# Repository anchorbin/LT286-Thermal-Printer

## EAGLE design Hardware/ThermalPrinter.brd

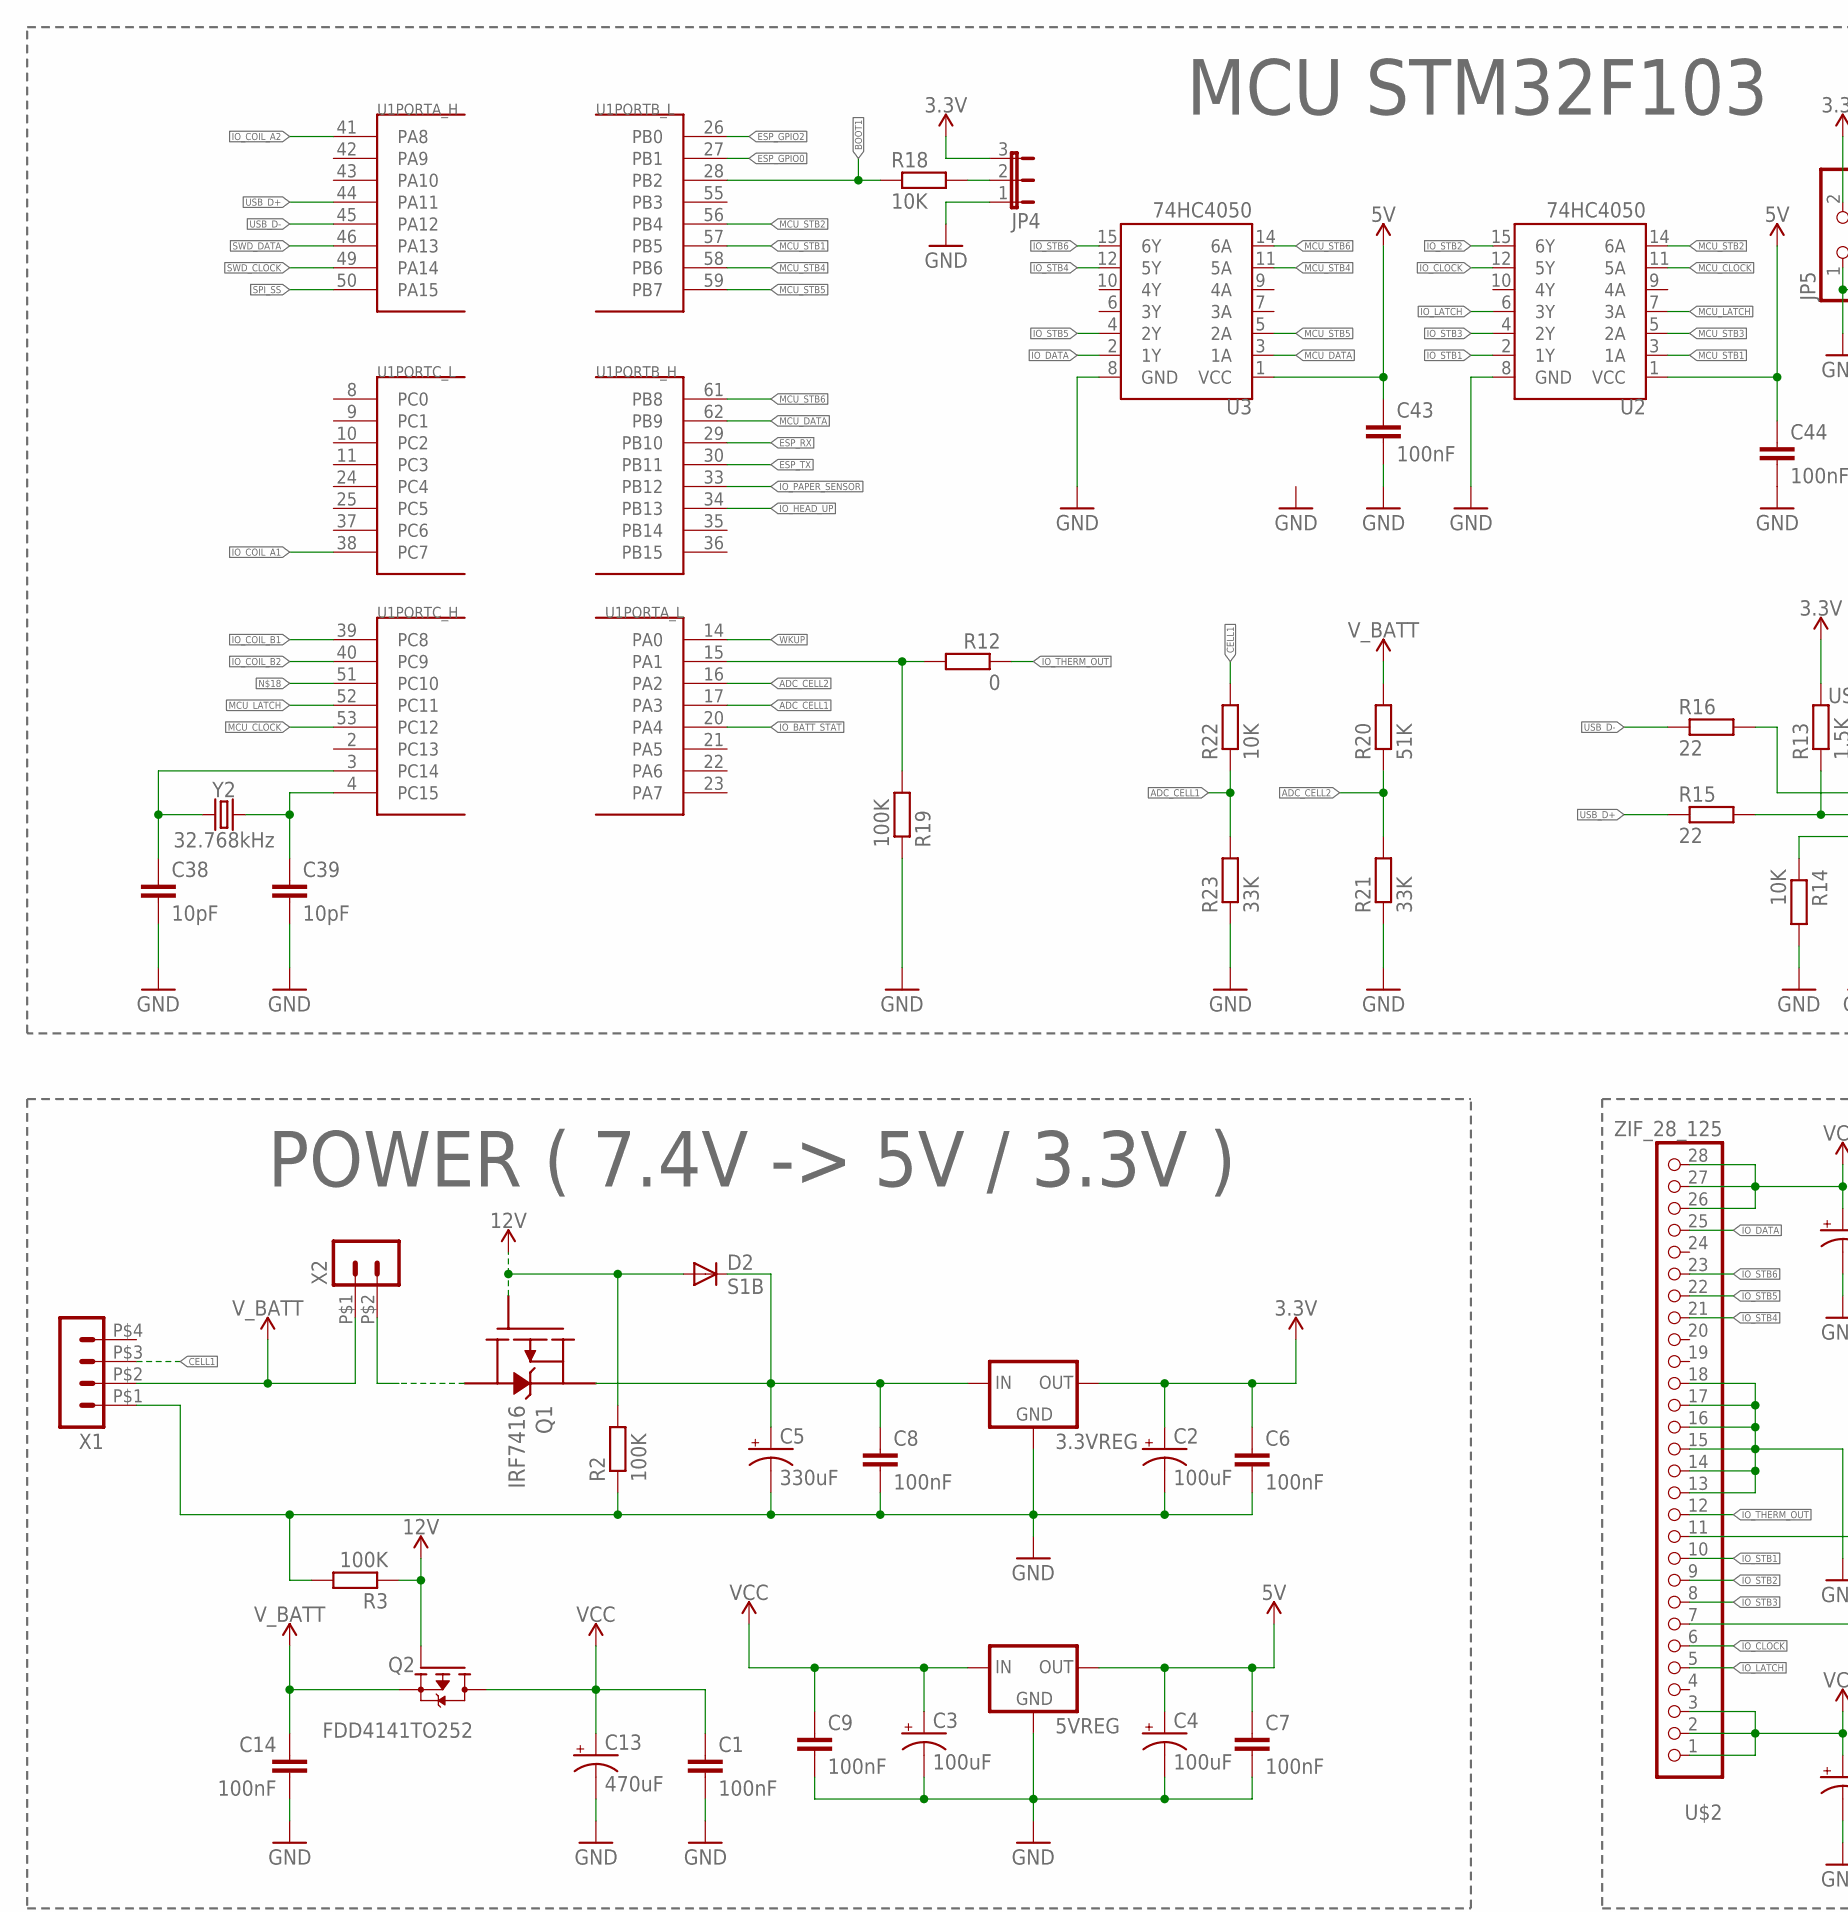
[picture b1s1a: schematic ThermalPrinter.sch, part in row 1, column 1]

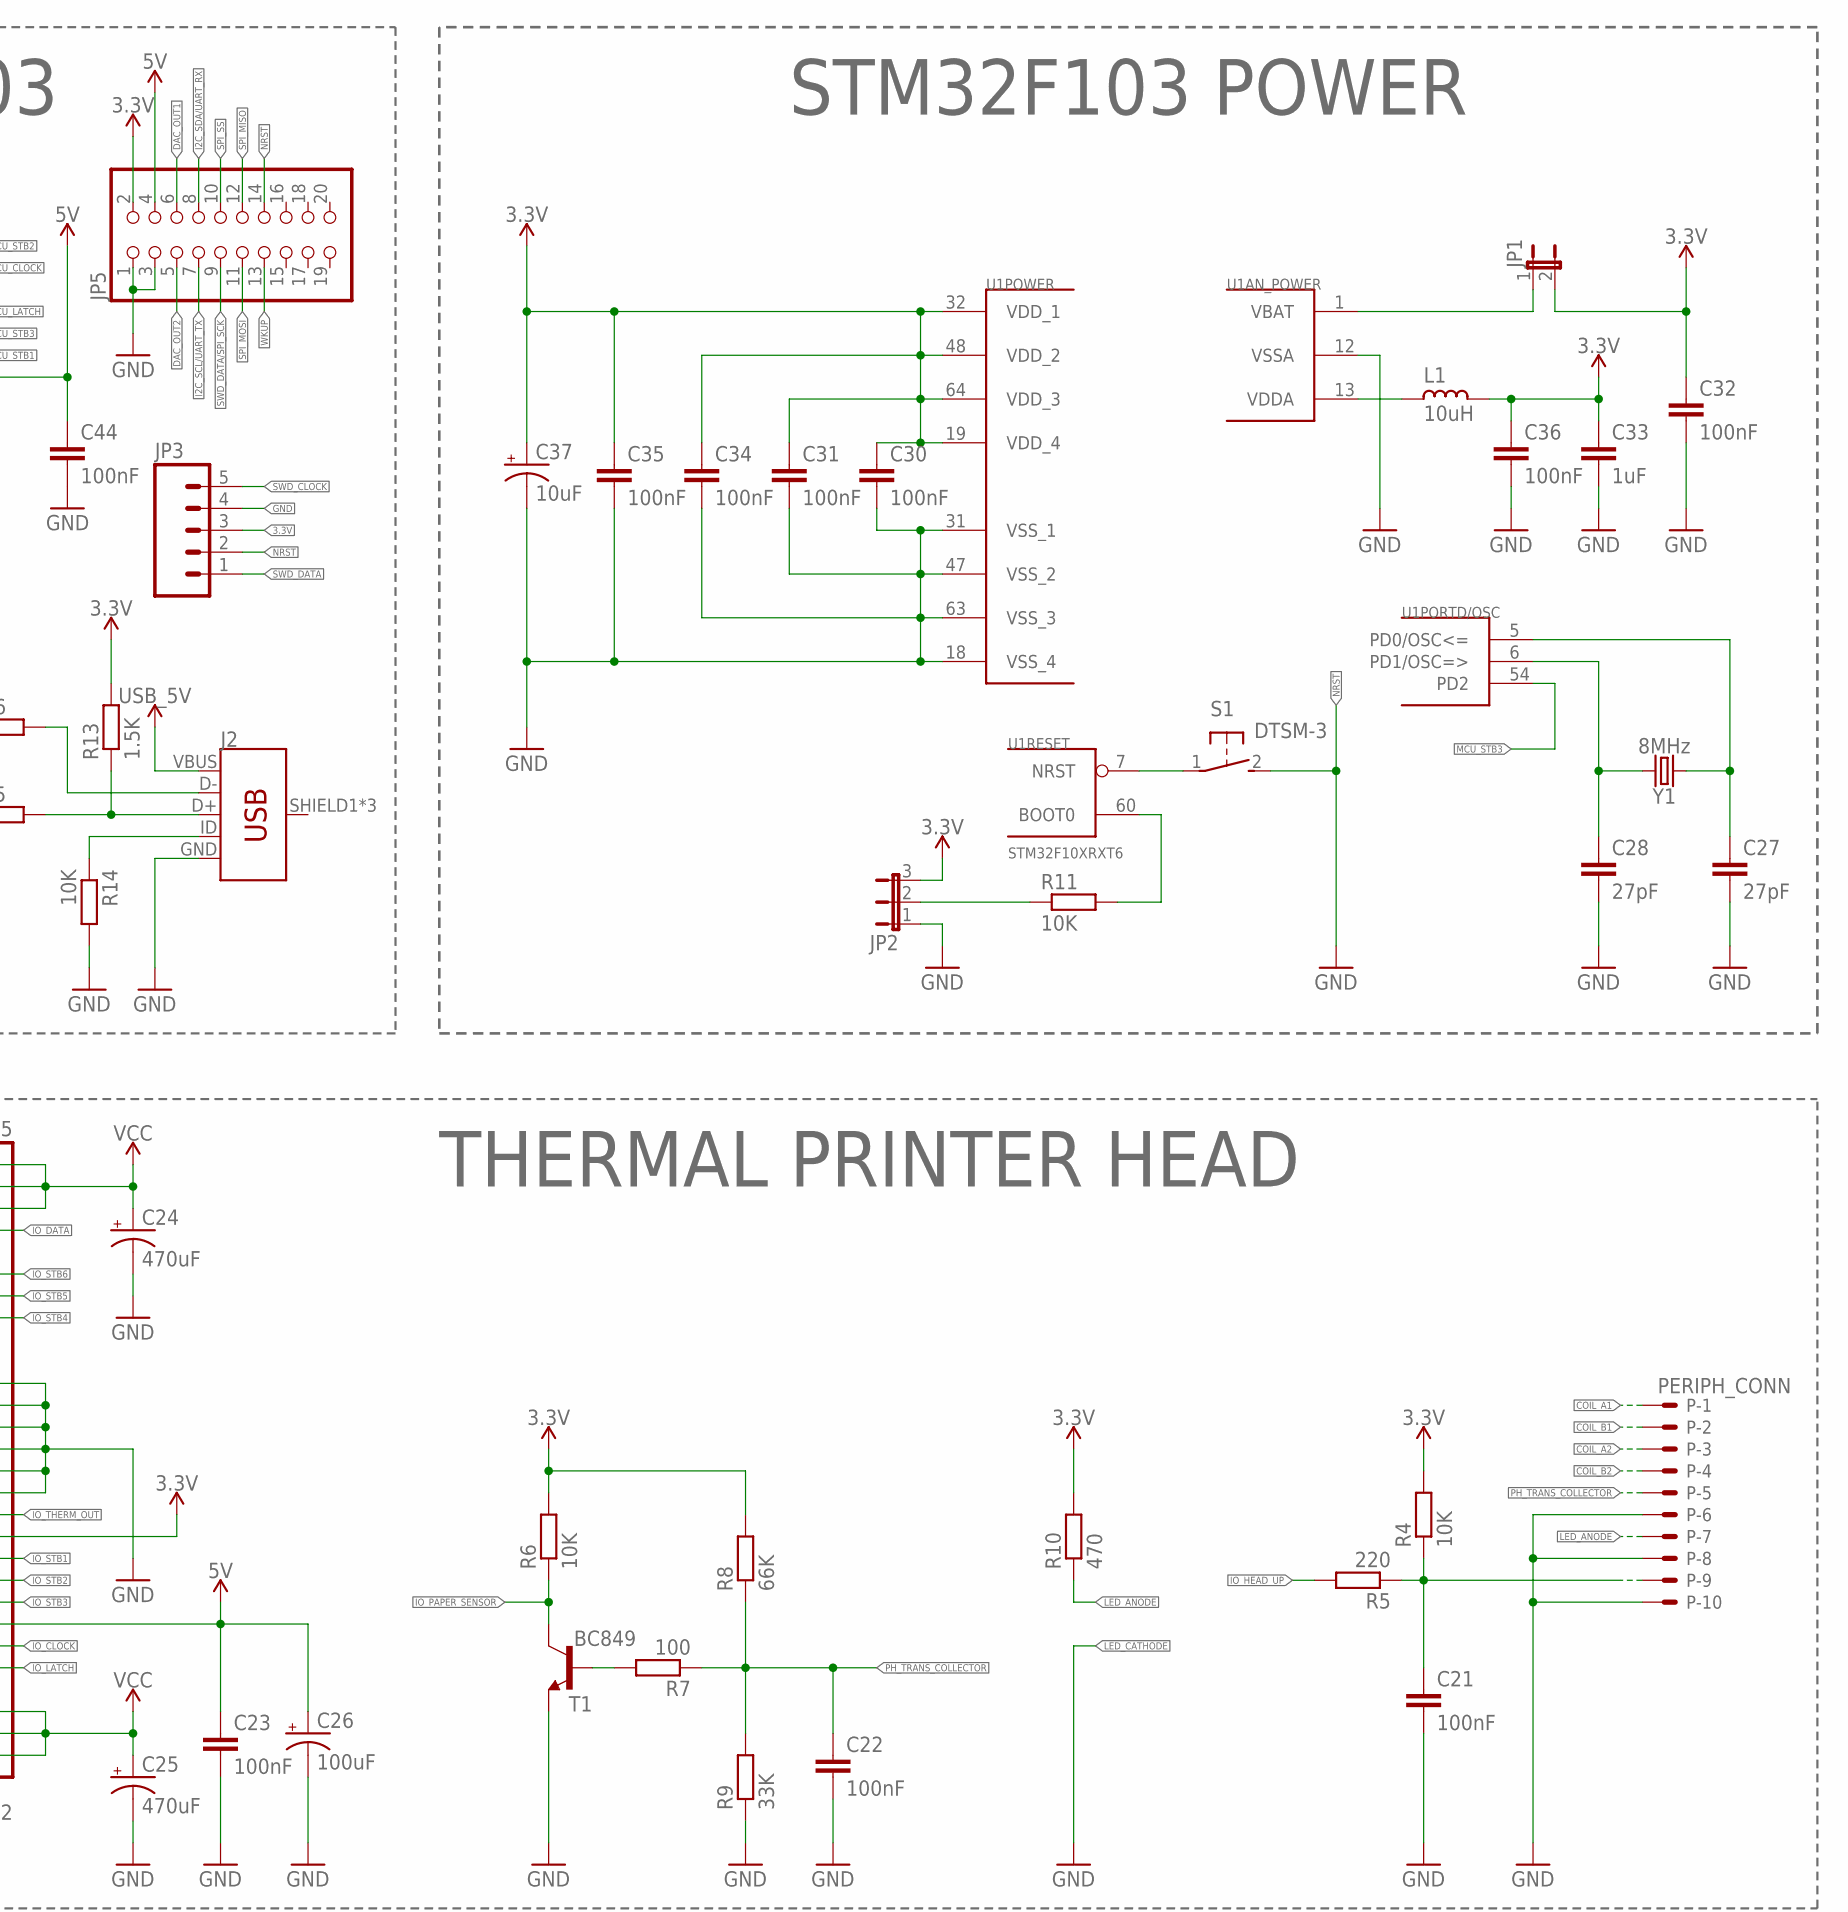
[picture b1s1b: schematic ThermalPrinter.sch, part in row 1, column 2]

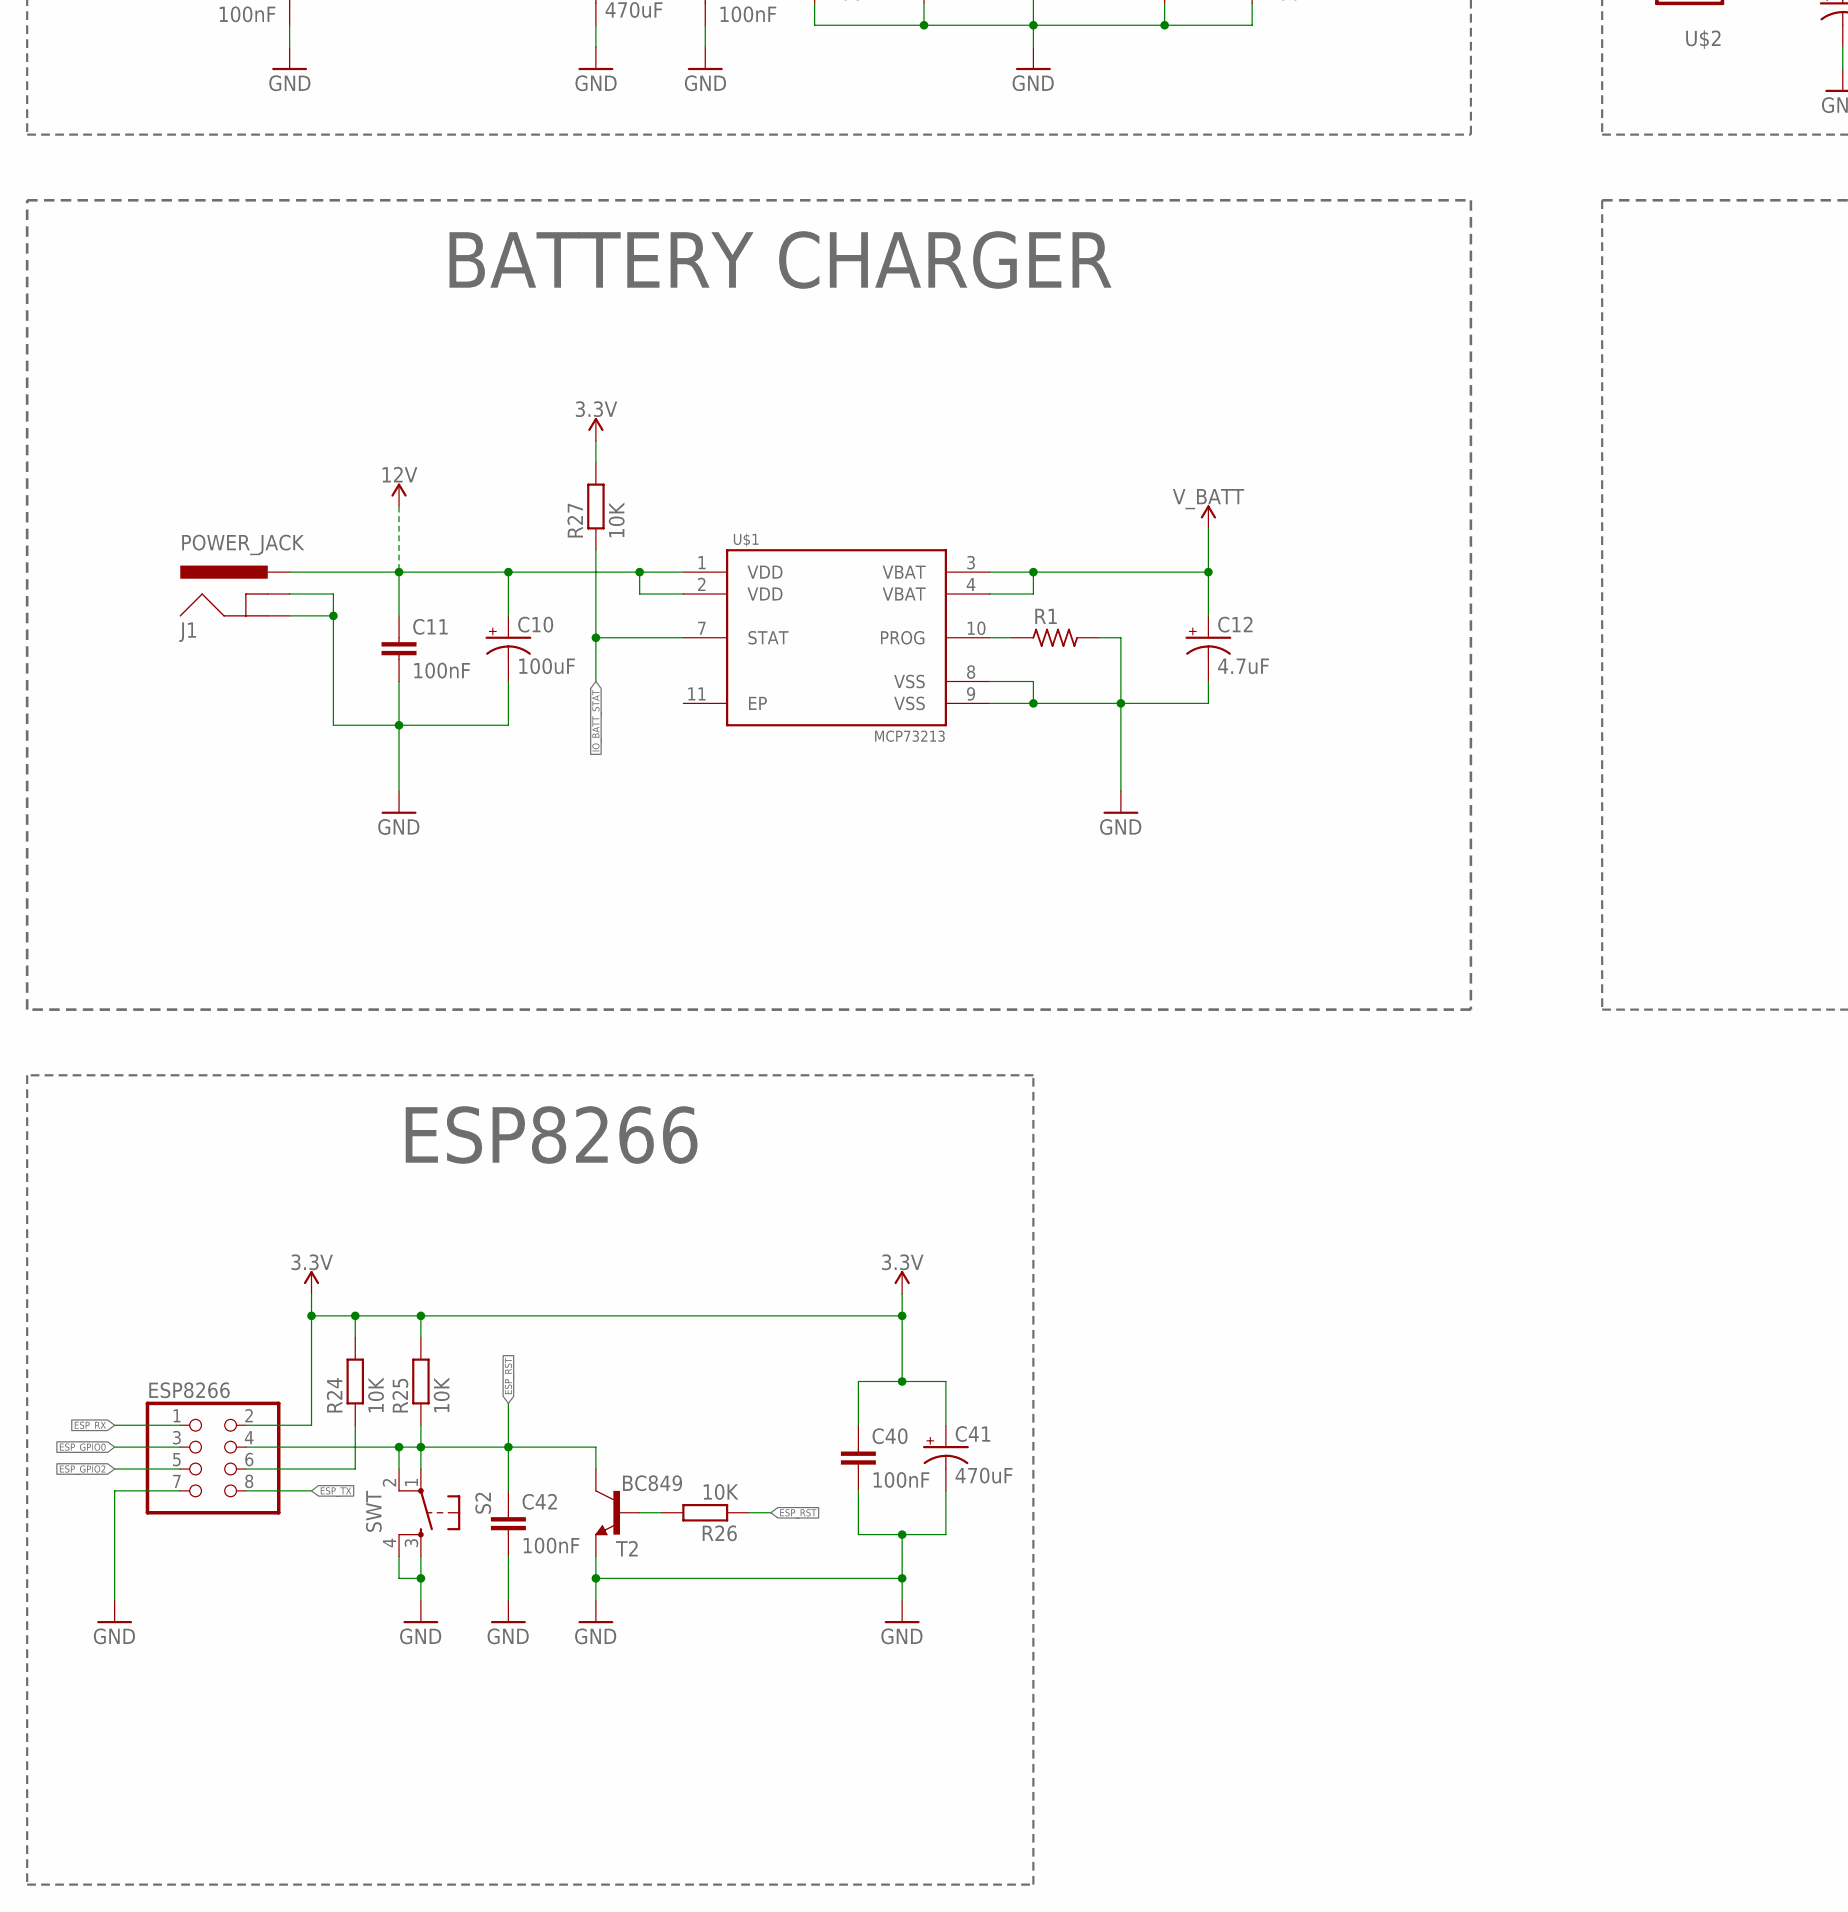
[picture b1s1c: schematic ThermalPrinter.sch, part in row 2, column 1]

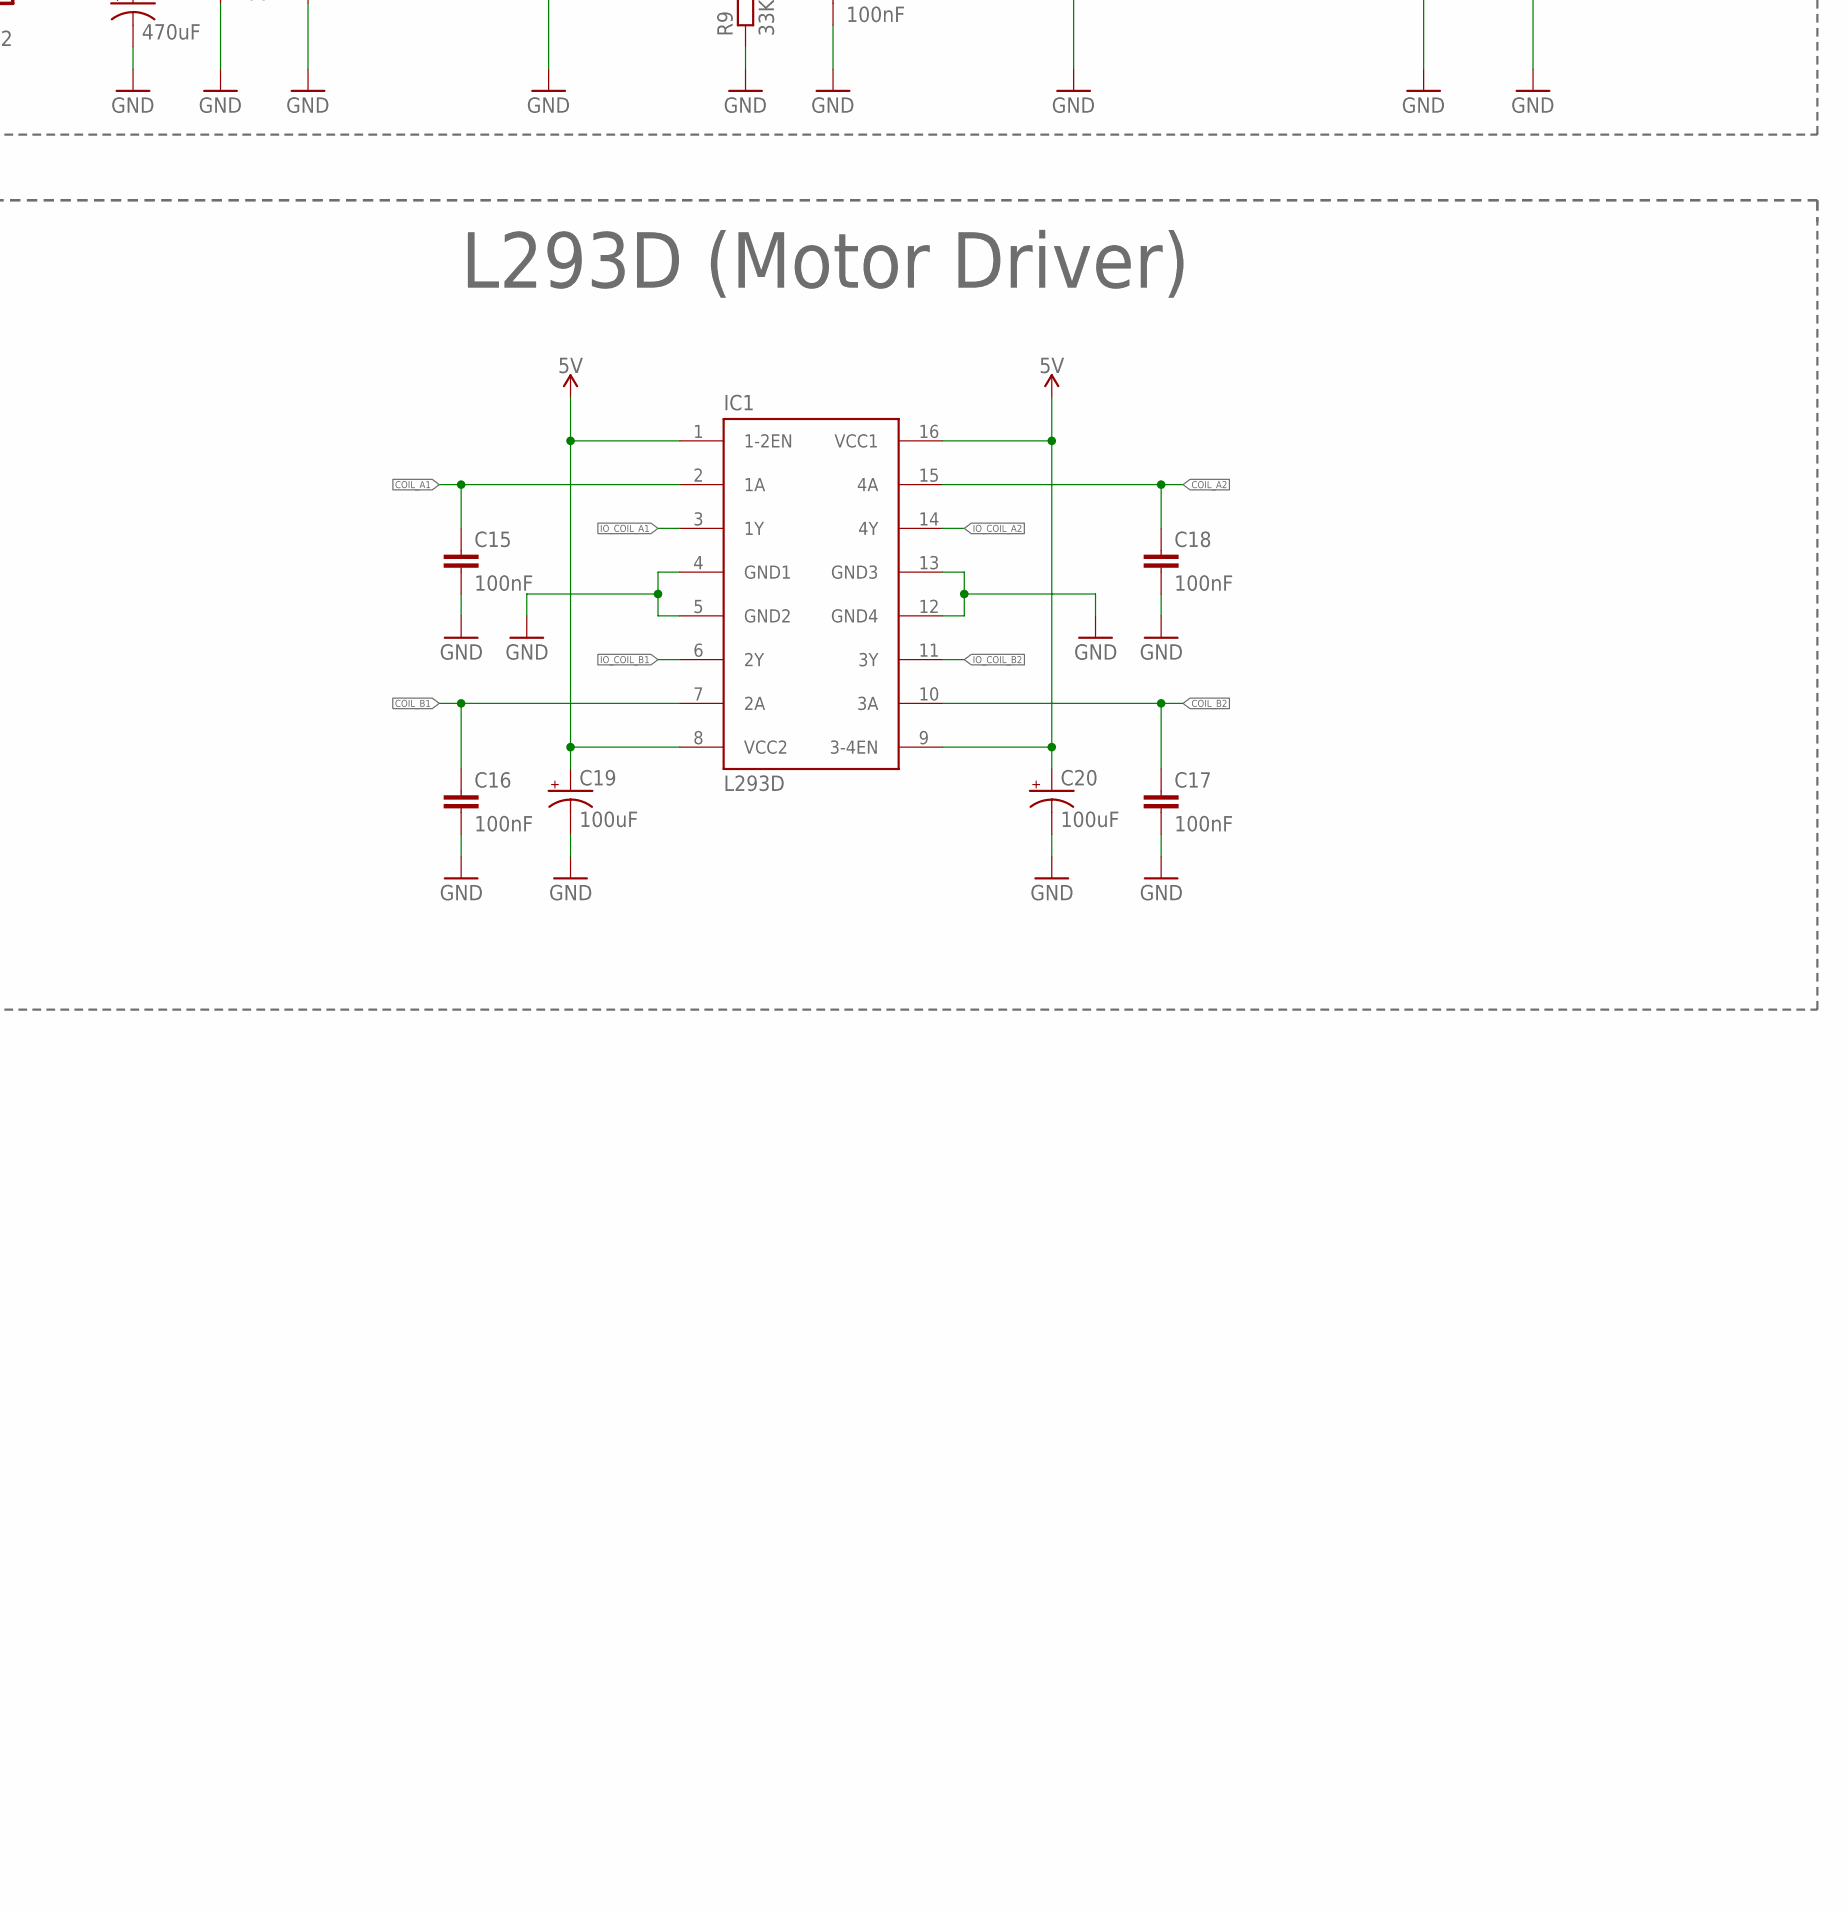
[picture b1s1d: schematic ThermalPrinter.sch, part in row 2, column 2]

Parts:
3.3VREG, 5VREG: LM1117TO252; TO252
C1, C6, C7, C8, C9, C11, C14, C15, C16, C17, C18, C21, C22, C23, C30, C31, C32, C34, C35, C36, C40, C42, C43, C44: 100nF; C0805K
C2, C3, C4, C10, C19, C20, C26: 100uF; CPOL-RADIAL-2.5MM-6.5MM
C5: 330uF; CPOL-RADIAL-2.5MM-6.5MM
C12: 4.7uF; CPOL-RADIAL-2.5MM-6.5MM
C13, C24, C25, C41: 470uF; CPOL-RADIAL-2.5MM-6.5MM
C27, C28: 27pF; C0603
C33: 1uF; 1206
C37: 10uF; EIA3216
C38, C39: 10pF; C0603
D2: S1B; DO214AC
ESP8266: PINHD-2X4; 2X04
IC1: L293D; DIL16
J1: POWER_JACK; POWER_JACK_PTH
J2: USB_MICRO-B_FEMALE-SMT; USB-B-MICRO-SMD
JP1: JP1E; JP1
JP2, JP4: JP2E; JP2
JP3: M05PTH; 1X05
JP5: PINHD-2X10; 2X10
L1: 10uH; L0603
P: PERIPH_CONN; 53261-10
Q1: IRF7416; SO8-IRFET-1
Q2: FDD4141TO252; TO252
R1: R_0805; R0805
R2, R3: 100K; R0805
R4, R6, R11, R14, R18, R22, R24, R25, R26, R27: 10K; R0603
R5: 220; R0603
R7: 100; R0603
R8: 66K; R0603
R9, R21, R23: 33K; R0603
R10: 470; R0603
R12: 0; R0603
R13: 1.5K; R0603
R15, R16: 22; R0603
R19: 100K; R0603
R20: 51K; R0603
S1: DTSM-3
S2: SWT; TACTILE-SWITCH-SMD
T1, T2: BC849; SOT23
U1: STM32F10XRXT6; TQFP64
U2, U3: 74HC4050; SO16
U$1: MCP73213
U$2: ZIF_28_125; ZIF_CONN_125
X1: HEADER_POS4_44914-0401; 44914-0401
X2: HEADER_POS2_43650-0215; 43650-0215
Y1: 8MHz; HC49UP
Y2: 32.768kHz; CRYSTAL-SMD-2X6-CYL

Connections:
3.3V: 3.3VREG.3 (OUT), C2.1 (+), C6.1, C30.1, C31.1, C32.1, C33.1, C34.1, C35.1, C36.1, C37.A (+), C40.1, C41.1 (+), ESP8266.2, JP1.2, JP2.3, JP3.3, JP4.3, JP5.2, L1.1, R4.2, R6.2, R8.2, R10.2, R13.2, R24.2, R25.2, R27.2, U1.19 (VDD_4), U1.32 (VDD_1), U1.48 (VDD_2), U1.64 (VDD_3), U$2.11
5V: 5VREG.3 (OUT), C4.1 (+), C7.1, C19.1 (+), C20.1 (+), C23.1, C26.1 (+), C43.1, C44.1, IC1.1 (1-2EN), IC1.8 (VCC2), IC1.9 (3-4EN), IC1.16 (VCC1), JP5.4, U2.1 (VCC), U3.1 (VCC), U$2.7
12V: C10.1 (+), C11.1, D2.A, J1.PWR, Q1.GATE (G), Q2.1 (G), R2.2, R3.1, U$1.1 (VDD), U$1.2 (VDD)
ADC_CELL1: R22.1, R23.2, U1.17 (PA3)
ADC_CELL2: R20.1, R21.2, U1.16 (PA2)
BOOT1: R18.1, U1.28 (PB2)
CELL1: R22.2, X1.P$3 (3)
COIL_A1: C15.1, IC1.2 (1A), P.1
COIL_A2: C18.1, IC1.15 (4A), P.3
COIL_B1: C16.1, IC1.7 (2A), P.2
COIL_B2: C17.1, IC1.10 (3A), P.4
D+: J2.D+, R13.1, R15.2
DAC_OUT1: JP5.6
DAC_OUT2: JP5.5
ESP_CH_PD: ESP8266.6, R24.1
ESP_GPIO0: ESP8266.3, U1.27 (PB1)
ESP_GPIO2: ESP8266.5, U1.26 (PB0)
ESP_RST: C42.1, ESP8266.4, R25.1, R26.1, S2.1, S2.2, T2.3 (C)
ESP_RX: ESP8266.1, U1.29 (PB10)
ESP_TX: ESP8266.8, U1.30 (PB11)
GND: 3.3VREG.1 (GND), 5VREG.1 (GND), C1.2, C2.2 (-), C3.2 (-), C4.2 (-), C5.2 (-), C6.2, C7.2, C8.2, C9.2, C10.2 (-), C11.2, C12.2 (-), C13.2 (-), C14.2, C15.2, C16.2, C17.2, C18.2, C19.2 (-), C20.2 (-), C21.2, C22.2, C23.2, C24.2 (-), C25.2 (-), C26.2 (-), C27.2, C28.2, C30.2, C31.2, C32.2, C33.2, C34.2, C35.2, C36.2, C37.C (-), C38.2, C39.2, C40.2, C41.2 (-), C42.2, C43.2, C44.2, ESP8266.7, IC1.4 (GND1), IC1.5 (GND2), IC1.12 (GND4), IC1.13 (GND3), J1.GND, J1.GNDBREAK, J2.GND, JP2.1, JP3.4, JP4.1, JP5.1, JP5.3, P.6, P.8, P.10, R1.2, R2.1, R3.2, R9.1, R14.2, R19.1, R21.1, R23.1, S2.3, S2.4, T1.2 (E), T2.2 (E), U1.12 (VSSA), U1.18 (VSS_4), U1.31 (VSS_1), U1.47 (VSS_2), U1.63 (VSS_3), U2.8 (GND), U3.8 (GND), U$1.8 (VSS), U$1.9 (VSS), U$2.13, U$2.14, U$2.15, U$2.16, U$2.17, U$2.18, X1.P$1 (1)
HEAD_UP_IN: C21.1, P.9, R4.1, R5.1
I2C_SCL/UART_TX: JP5.7
I2C_SDA/UART_RX: JP5.8
IO_BATT_STAT: R27.1, U1.20 (PA4), U$1.7 (STAT)
IO_CLOCK: U2.12 (5Y), U$2.6
IO_COIL_A1: IC1.3 (1Y), U1.38 (PC7)
IO_COIL_A2: IC1.14 (4Y), U1.41 (PA8)
IO_COIL_B1: IC1.6 (2Y), U1.39 (PC8)
IO_COIL_B2: IC1.11 (3Y), U1.40 (PC9)
IO_DATA: U3.2 (1Y), U$2.25
IO_HEAD_UP: R5.2, U1.34 (PB13)
IO_LATCH: U2.6 (3Y), U$2.5
IO_PAPER_SENSOR: R6.1, T1.3 (C), U1.33 (PB12)
IO_STB1: U2.2 (1Y), U$2.10
IO_STB2: U2.15 (6Y), U$2.9
IO_STB3: U2.4 (2Y), U$2.8
IO_STB4: U3.12 (5Y), U$2.21
IO_STB5: U3.4 (2Y), U$2.22
IO_STB6: U3.15 (6Y), U$2.23
IO_THERM_OUT: R12.1, U$2.12
LED_ANODE: P.7, R10.1
MCU_CLOCK: U1.53 (PC12), U2.11 (5A)
MCU_DATA: U1.62 (PB9), U3.3 (1A)
MCU_LATCH: U1.52 (PC11), U2.7 (3A)
MCU_STB1: U1.57 (PB5), U2.3 (1A)
MCU_STB2: U1.56 (PB4), U2.14 (6A)
MCU_STB3: U1.54 (PD2), U2.5 (2A)
MCU_STB4: U1.58 (PB6), U3.11 (5A)
MCU_STB5: U1.59 (PB7), U3.5 (2A)
MCU_STB6: U1.61 (PB8), U3.14 (6A)
unnamed: S1.1, U1.7 (NRST)
unnamed: 3.3VREG.2 (IN), C5.1 (+), C8.1, D2.C, Q1.SOURCE-1 (S)
unnamed: R7.2, T1.1 (B)
unnamed: R1.1, U$1.10 (PROG)
unnamed: C28.1, U1.6 (PD1/OSC=>), Y1.2
unnamed: L1.2, U1.13 (VDDA)
unnamed: C27.1, U1.5 (PD0/OSC<=), Y1.1
unnamed: JP1.1, U1.1 (VBAT)
unnamed: Q1.DRAIN-4 (D), X2.P$2 (2)
unnamed: C38.1, U1.3 (PC14), Y2.X2 (2)
unnamed: C39.1, U1.4 (PC15), Y2.X1 (1)
unnamed: J2.ID, R14.1
unnamed: J2.D-, R16.2
unnamed: JP4.2, R18.2
unnamed: R11.2, U1.60 (BOOT0)
unnamed: R26.2, T2.1 (B)
unnamed: JP2.2, R11.1
unnamed: R12.2, R19.2, U1.15 (PA1)
NRST: JP3.2, JP5.14, S1.2
PH_TRANS_COLLECTOR: C22.1, P.5, R7.1, R8.1, R9.2
SPI_MISO: JP5.12
SPI_MOSI: JP5.11
SPI_SS: JP5.10, U1.50 (PA15)
SWD_CLOCK: JP3.5, U1.49 (PA14)
SWD_DATA: JP3.1, U1.46 (PA13)
SWD_DATA/SPI_SCK: JP5.9
USB_D+: R15.1, U1.44 (PA11)
USB_D-: R16.1, U1.45 (PA12)
VCC: 5VREG.2 (IN), C1.1, C3.1 (+), C9.1, C13.1 (+), C24.1 (+), C25.1 (+), Q2.3 (D), U$2.1, U$2.2, U$2.3, U$2.26, U$2.27, U$2.28
VCC_2: J2.VBUS
V_BATT: C12.1 (+), C14.1, Q2.2 (S), R20.2, U$1.3 (VBAT), U$1.4 (VBAT), X1.P$2 (2), X2.P$1 (1)
WKUP: JP5.13, U1.14 (PA0)

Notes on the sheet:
MCU STM32F103
L293D (Motor Driver)
POWER ( 7.4V -> 5V / 3.3V )
THERMAL PRINTER HEAD
ESP8266
BATTERY CHARGER
STM32F103 POWER

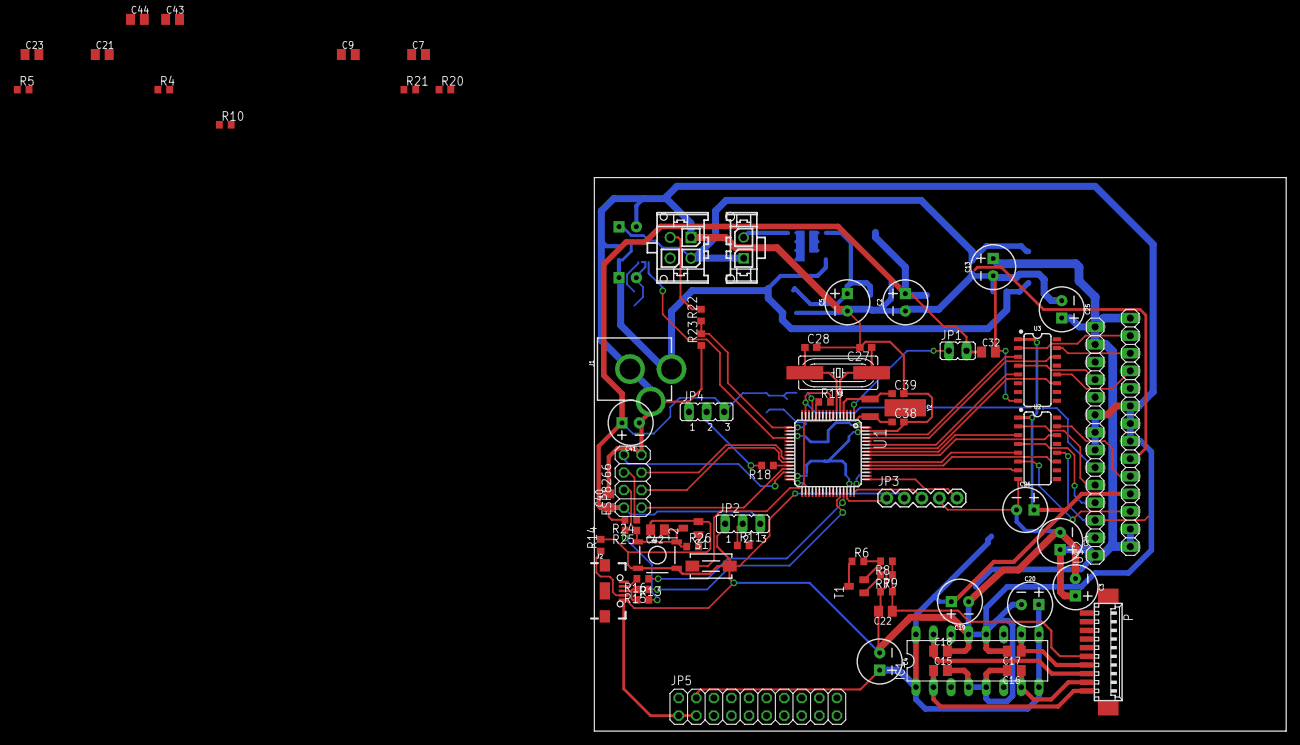
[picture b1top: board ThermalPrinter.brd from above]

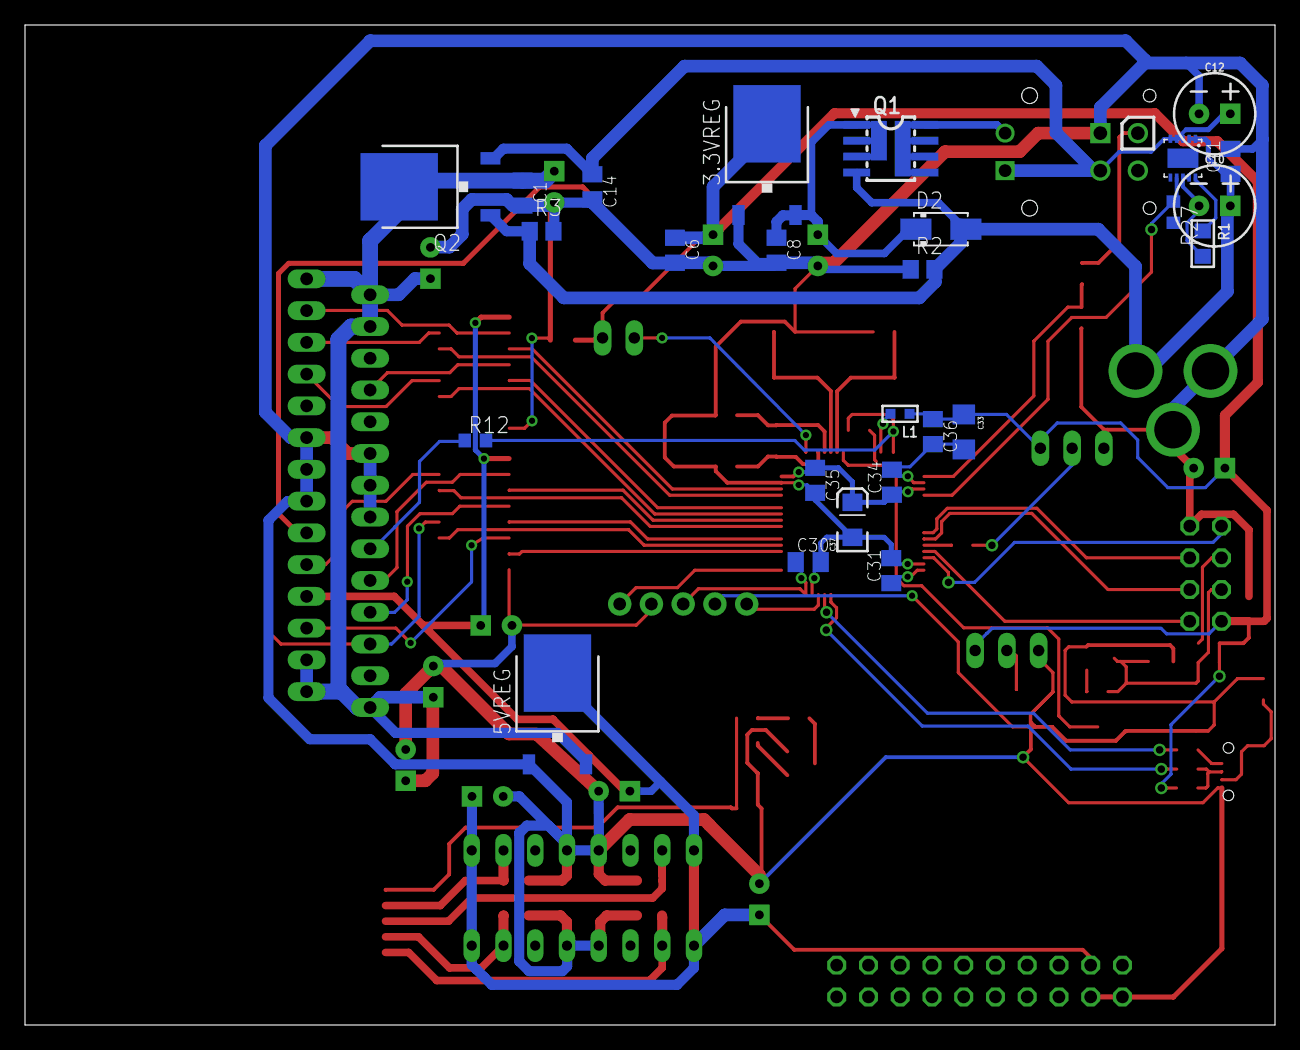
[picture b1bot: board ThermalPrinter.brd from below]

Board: 2 copper layers, 100.0 x 80.0 mm, 98 parts (26 on the bottom side), 75 nets.

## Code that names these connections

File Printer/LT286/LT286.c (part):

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	LT286.StrobeIndex = 0;
	LT286.BitOrder = MSB;

	LT286.LatchPin = (IO){ MCU_LATCH_GPIO_Port, MCU_LATCH_Pin };
	LT286.DataPin = (IO){ MCU_DATA_GPIO_Port, MCU_DATA_Pin };
	LT286.ClockPin = (IO){ MCU_CLOCK_GPIO_Port, MCU_CLOCK_Pin };

	LT286.MotorA = (IO){ IO_COIL_A1_GPIO_Port, IO_COIL_A1_Pin };
	LT286.MotorAn = (IO){ IO_COIL_A2_GPIO_Port, IO_COIL_A2_Pin };
	LT286.MotorB = (IO){ IO_COIL_B1_GPIO_Port, IO_COIL_B1_Pin };
	LT286.MotorBn = (IO){ IO_COIL_B2_GPIO_Port, IO_COIL_B2_Pin };

	LT286.StrobePin[0] = (IO){ MCU_STB1_GPIO_Port, MCU_STB1_Pin };
	LT286.StrobePin[1] = (IO){ MCU_STB2_GPIO_Port, MCU_STB2_Pin };
	LT286.StrobePin[2] = (IO){ MCU_STB3_GPIO_Port, MCU_STB3_Pin };
	LT286.StrobePin[3] = (IO){ MCU_STB4_GPIO_Port, MCU_STB4_Pin };
	LT286.StrobePin[4] = (IO){ MCU_STB5_GPIO_Port, MCU_STB5_Pin };
	LT286.StrobePin[5] = (IO){ MCU_STB6_GPIO_Port, MCU_STB6_Pin };

	LT286.HeadUp = (IO){ IO_HEAD_GPIO_Port, IO_HEAD_Pin };
	LT286.PaperSensor = (IO){ IO_PAPER_GPIO_Port, IO_PAPER_Pin };
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
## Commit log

2020-05-01 LT286 Thermal Printer with ability to download and print images and text from external website using ESP8266 Wi-Fi module.
2020-05-01 Added printer schematic and PCB.

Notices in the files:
parts and their libraries:
SparkFun-Capacitors: Licensing: Creative Commons ShareAlike 4.0 International - https://creativecommons.org/licenses/by-sa/4.0
rc-master-smd: Copyright (C) 2007, Bob Starr
SparkFun: Licensing: CC v3.0 Share-Alike You are welcome to use this library for commercial purposes.
